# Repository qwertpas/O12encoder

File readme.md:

## Compact magnetic encoder on RS485 bus

Intended to work with [squirrelbrain](https://github.com/qwertpas/squirrelbrain) as part of the [Pintobotics](https://pintobotics.substack.com) project.

Magnetic sensor: [MA702](https://www.monolithicpower.com/en/ma702.html)

MCU: [STM32L011F4U](https://www.digikey.com/en/products/detail/stmicroelectronics/STM32L011F4U6TR/6166960)

Size: 14.04mm x 14.04mm

Mounting: 6x M2 on 12mm diameter circle, four distributed on square and three distributed on an equilateral triangle (for certain small drone motors)

Connection: 2x 4pin 0.5mm pitch FFC for power and RS485 communication (daisy chainable)

Alternate connection: 2x SPI solder pads, aux GPIO/ADC

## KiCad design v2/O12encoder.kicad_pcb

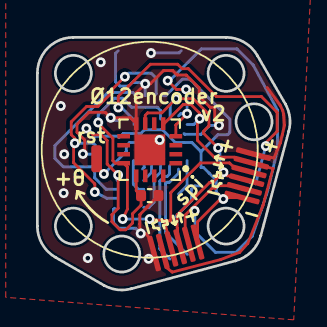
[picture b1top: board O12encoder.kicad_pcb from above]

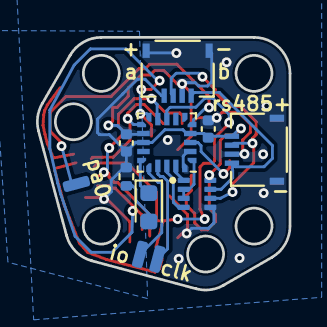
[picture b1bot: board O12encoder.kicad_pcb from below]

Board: 2 copper layers, 14.0 x 14.0 mm, 16 parts (11 on the bottom side), 17 nets.

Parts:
C1, C2, C3: 1uF; C_0402_1005Metric
D1: LED_Small; LED_0603_1608Metric
J1, J2: Conn_01x06_Pin; FFC_0.5mm_6p
J3, J4: Conn_01x04; TE_2328702-4
R1: R_Small_US; R_0402_1005Metric
TP1, TP2, TP3, TP4: TestPoint; TestPoint_Pad_Rect
U1: MA702GQ-P
U2: STM32L011F4Ux; ST_UFQFPN-20_3x3mm_P0.5mm
U3: THVD1420DRLR; THVD1420DRLR_SOT-585

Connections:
+3.3V: C1.1, C2.1, C3.1, J1.6, J2.6, J3.1, J4.1, R1.1, U1.13 (VDD), U2.4 (VDDA), U2.13 (VDD), U3.8 (VCC)
/ADC_IN0/WKUP: TP4.1, U2.5 (PA0)
/NRST: TP1.1, U2.3 (NRST)
/RS485_A: J3.2, J4.2, U3.6 (A)
/RS485_B: J3.4, J4.4, U3.7 (B)
/SPI_MISO: J1.4, J2.4, U1.7 (MISO), U2.9 (PA6)
/SPI_MOSI: J1.5, J2.5, U1.4 (MOSI), U2.10 (PA7)
/SPI_SCLK: J1.3, J2.3, U1.12 (SCLK), U2.8 (PA5)
/SWCLK: TP3.1, U2.17 (PA14)
/SWDIO: TP2.1, U2.16 (PA13)
/UART_DE: U2.1 (PC14), U3.2 (~RE), U3.3 (DE)
/UART_RX: U2.19 (PB7), U3.1 (R)
/UART_TX: U2.18 (PB6), U3.4 (D)
/~MAG2_CS: J1.2, J2.2, U1.5 (CS), U2.11 (PB1)
GND: C1.2, C2.2, C3.2, J1.1, J2.1, J3.3, J3.MP (MountPin), J4.3, J4.MP (MountPin), U1.8 (GND), U1.17 (PAD), U2.2 (PC15), U2.12 (VSS), U2.20 (PB9), U3.5 (GND)
unnamed: D1.2 (A), R1.2
unnamed: D1.1 (K), U2.15 (PA10)

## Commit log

2024-03-10 readme
2024-03-11 readme, gen pdf
2024-04-15 Add MIT LICENSE
